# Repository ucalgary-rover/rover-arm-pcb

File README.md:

# rover-arm-pcb

A custom robot arm control PCB for the 2023 SSRT rover.

## Features
* Onboard microcontroller breakout board, like an Arduino Mega or similar
* Controls up to:
    * 7x NEMA23 stepper motors
    * 2x servo motors
    * 7x limit switches
    * A spotlight
    * Other peripherals, like grip strength load cell sensors
* Per-motor current sensing capabilities
* Integrates with off-the-shelf stepper motor drivers (TB6560) and custom circuitry for high reliability and ease of assembly

## Methodology
* PCB is designed in KiCAD v7.0.
* PCB design is used as a teaching tool, so simplicity and likelihood of success was prioritized

## Dependencies
https://github.com/Alarm-Siren/arduino-kicad-library

## Opportunities for Impovement
* Use an encoder/decoder for the EN pins, instead of using so many pins on the microcontroller.

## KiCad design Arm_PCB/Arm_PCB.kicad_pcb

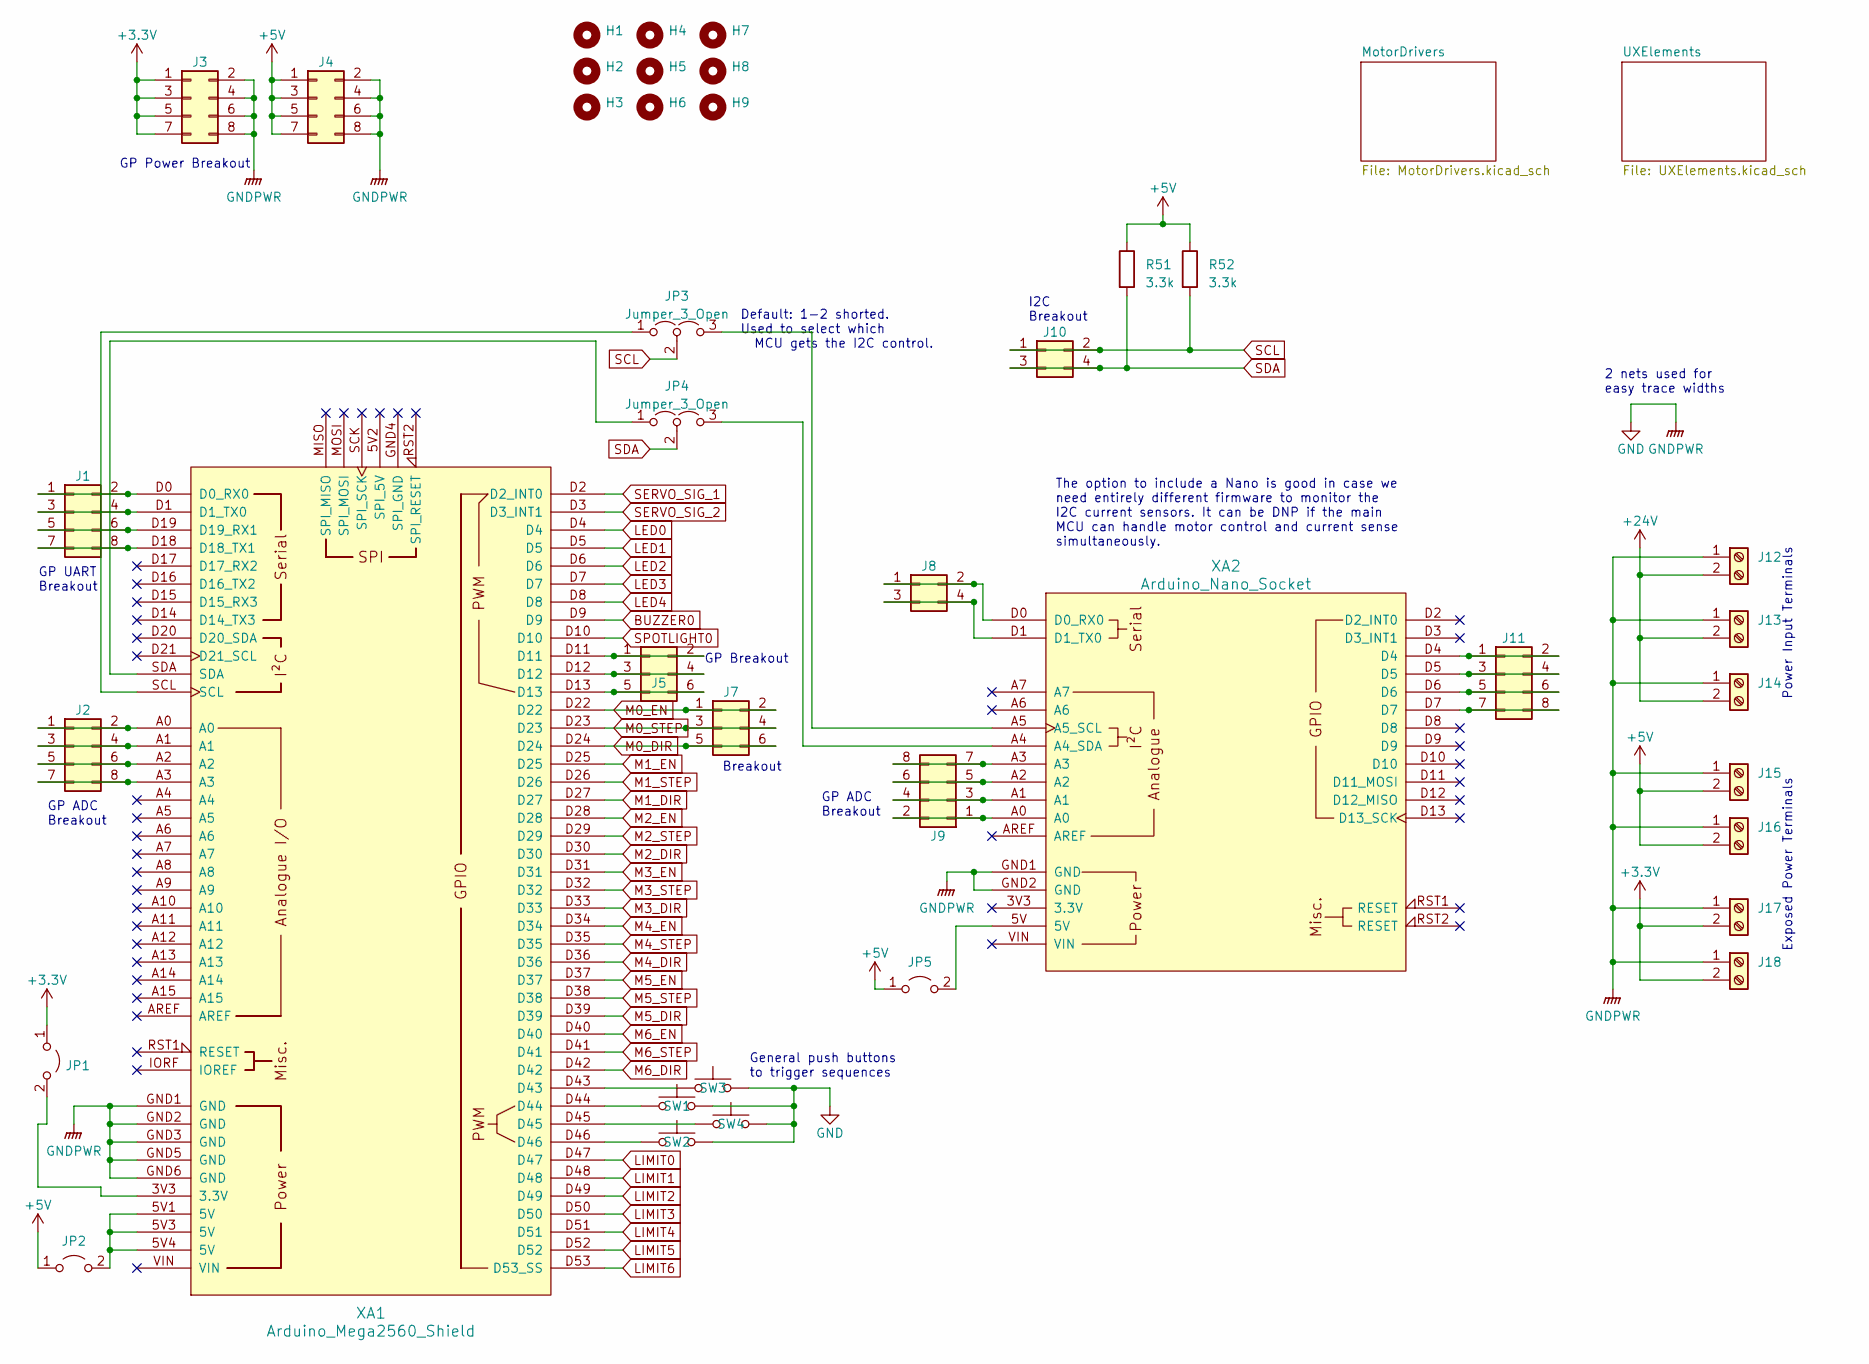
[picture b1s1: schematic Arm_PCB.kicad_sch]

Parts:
H1, H2, H3, H4, H5, H6, H7, H8, H9: MountingHole; MountingHole_4.3mm_M4
J1, J2, J3, J4, J9, J11: Conn_02x04_Counter_Clockwise; PinHeader_2x04_P2.54mm_Vertical
J5, J7: Conn_02x03_Counter_Clockwise; PinHeader_2x03_P2.54mm_Vertical
J8, J10: Conn_02x02_Counter_Clockwise; PinHeader_2x02_P2.54mm_Vertical
J12, J13, J14, J15, J16, J17, J18: Screw_Terminal_01x02; TerminalBlock_bornier-2_P5.08mm
JP1, JP2, JP5: Jumper_2_Open; PinHeader_1x02_P2.54mm_Vertical
JP3, JP4: Jumper_3_Open; PinHeader_1x03_P2.54mm_Vertical
R51, R52: 3.3k; R_1206_3216Metric_Pad1.30x1.75mm_HandSolder
SW1, SW2, SW3, SW4: SW_Push; SW_PUSH_6mm
XA1: Arduino_Mega2560_Shield
XA2: Arduino_Nano_Socket

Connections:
+3.3V: J3.1, J3.3, J3.5, J3.7, J17.2, J18.2, JP1.1 (A); also elsewhere on the board
+5V: J4.1, J4.3, J4.5, J4.7, J15.2, J16.2, JP2.1 (A), JP5.1 (A), R51.1, R52.1; also elsewhere on the board
+24V: J12.2, J13.2, J14.2; also elsewhere on the board
BUZZER0: XA1.D9; also elsewhere on the board
GND: J3.2, J3.4, J3.6, J3.8, J4.2, J4.4, J4.6, J4.8, J12.1, J13.1, J14.1, J15.1, J16.1, J17.1, J18.1, SW1.2, SW2.2, SW3.2, SW4.2, XA1.GND1 (GND), XA1.GND2 (GND), XA1.GND3 (GND), XA1.GND5 (GND), XA1.GND6 (GND), XA2.GND1 (GND), XA2.GND2 (GND); also elsewhere on the board
LED0: XA1.D4; also elsewhere on the board
LED1: XA1.D5; also elsewhere on the board
LED2: XA1.D6; also elsewhere on the board
LED3: XA1.D7; also elsewhere on the board
LED4: XA1.D8; also elsewhere on the board
LIMIT0: XA1.D47; also elsewhere on the board
LIMIT1: XA1.D48; also elsewhere on the board
LIMIT2: XA1.D49; also elsewhere on the board
LIMIT3: XA1.D50; also elsewhere on the board
LIMIT4: XA1.D51; also elsewhere on the board
LIMIT5: XA1.D52; also elsewhere on the board
LIMIT6: XA1.D53 (D53_SS); also elsewhere on the board
M0_DIR: J7.5, J7.6, XA1.D24; also elsewhere on the board
M0_EN: J7.1, J7.2, XA1.D22; also elsewhere on the board
M0_STEP: J7.3, J7.4, XA1.D23; also elsewhere on the board
M1_DIR: XA1.D27; also elsewhere on the board
M1_EN: XA1.D25; also elsewhere on the board
M1_STEP: XA1.D26; also elsewhere on the board
M2_DIR: XA1.D30; also elsewhere on the board
M2_EN: XA1.D28; also elsewhere on the board
M2_STEP: XA1.D29; also elsewhere on the board
M3_DIR: XA1.D33; also elsewhere on the board
M3_EN: XA1.D31; also elsewhere on the board
M3_STEP: XA1.D32; also elsewhere on the board
M4_DIR: XA1.D36; also elsewhere on the board
M4_EN: XA1.D34; also elsewhere on the board
M4_STEP: XA1.D35; also elsewhere on the board
M5_DIR: XA1.D39; also elsewhere on the board
M5_EN: XA1.D37; also elsewhere on the board
M5_STEP: XA1.D38; also elsewhere on the board
M6_DIR: XA1.D42; also elsewhere on the board
M6_EN: XA1.D40; also elsewhere on the board
M6_STEP: XA1.D41; also elsewhere on the board
unnamed: J1.1, J1.2, XA1.D0 (D0_RX0)
unnamed: J1.3, J1.4, XA1.D1 (D1_TX0)
unnamed: J1.5, J1.6, XA1.D19 (D19_RX1)
unnamed: J1.7, J1.8, XA1.D18 (D18_TX1)
unnamed: J2.1, J2.2, XA1.A0
unnamed: J2.3, J2.4, XA1.A1
unnamed: J2.5, J2.6, XA1.A2
unnamed: J2.7, J2.8, XA1.A3
unnamed: J5.1, J5.2, XA1.D11
unnamed: J5.3, J5.4, XA1.D12
unnamed: J5.5, J5.6, XA1.D13
unnamed: J8.1, J8.2, XA2.D0 (D0_RX0)
unnamed: J8.3, J8.4, XA2.D1 (D1_TX0)
unnamed: J9.1, J9.2, XA2.A0
unnamed: J9.3, J9.4, XA2.A1
unnamed: J9.5, J9.6, XA2.A2
unnamed: J9.7, J9.8, XA2.A3
unnamed: J11.1, J11.2, XA2.D4
unnamed: J11.3, J11.4, XA2.D5
unnamed: J11.5, J11.6, XA2.D6
unnamed: J11.7, J11.8, XA2.D7
unnamed: JP1.2 (B), XA1.3V3 (3.3V)
unnamed: JP2.2 (B), XA1.5V1 (5V), XA1.5V3 (5V), XA1.5V4 (5V)
unnamed: JP3.1 (A), XA1.SCL
unnamed: JP3.3 (B), XA2.A5 (A5_SCL)
unnamed: JP4.1 (A), XA1.SDA
unnamed: JP4.3 (B), XA2.A4 (A4_SDA)
unnamed: JP5.2 (B), XA2.5V
unnamed: SW1.1, XA1.D44
unnamed: SW2.1, XA1.D46
unnamed: SW3.1, XA1.D43
unnamed: SW4.1, XA1.D45
SCL: J10.1, J10.2, JP3.2 (C), R52.2; also elsewhere on the board
SDA: J10.3, J10.4, JP4.2 (C), R51.2; also elsewhere on the board
SERVO_SIG_1: XA1.D2 (D2_INT0); also elsewhere on the board
SERVO_SIG_2: XA1.D3 (D3_INT1); also elsewhere on the board
SPOTLIGHT0: XA1.D10; also elsewhere on the board

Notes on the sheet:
Exposed Power Terminals
The option to include a Nano is good in case we need entirely different firmware to monitor the I2C current sensors. It can be DNP if the main MCU can handle motor control and current sense simultaneously.
General push buttons to trigger sequences
GP UART Breakout
GP Breakout
Default: 1-2 shorted. Used to select which MCU gets the I2C control.
2 nets used for easy trace widths
GP Power Breakout
GP ADC Breakout
I2C Breakout
Breakout
Power Input Terminals

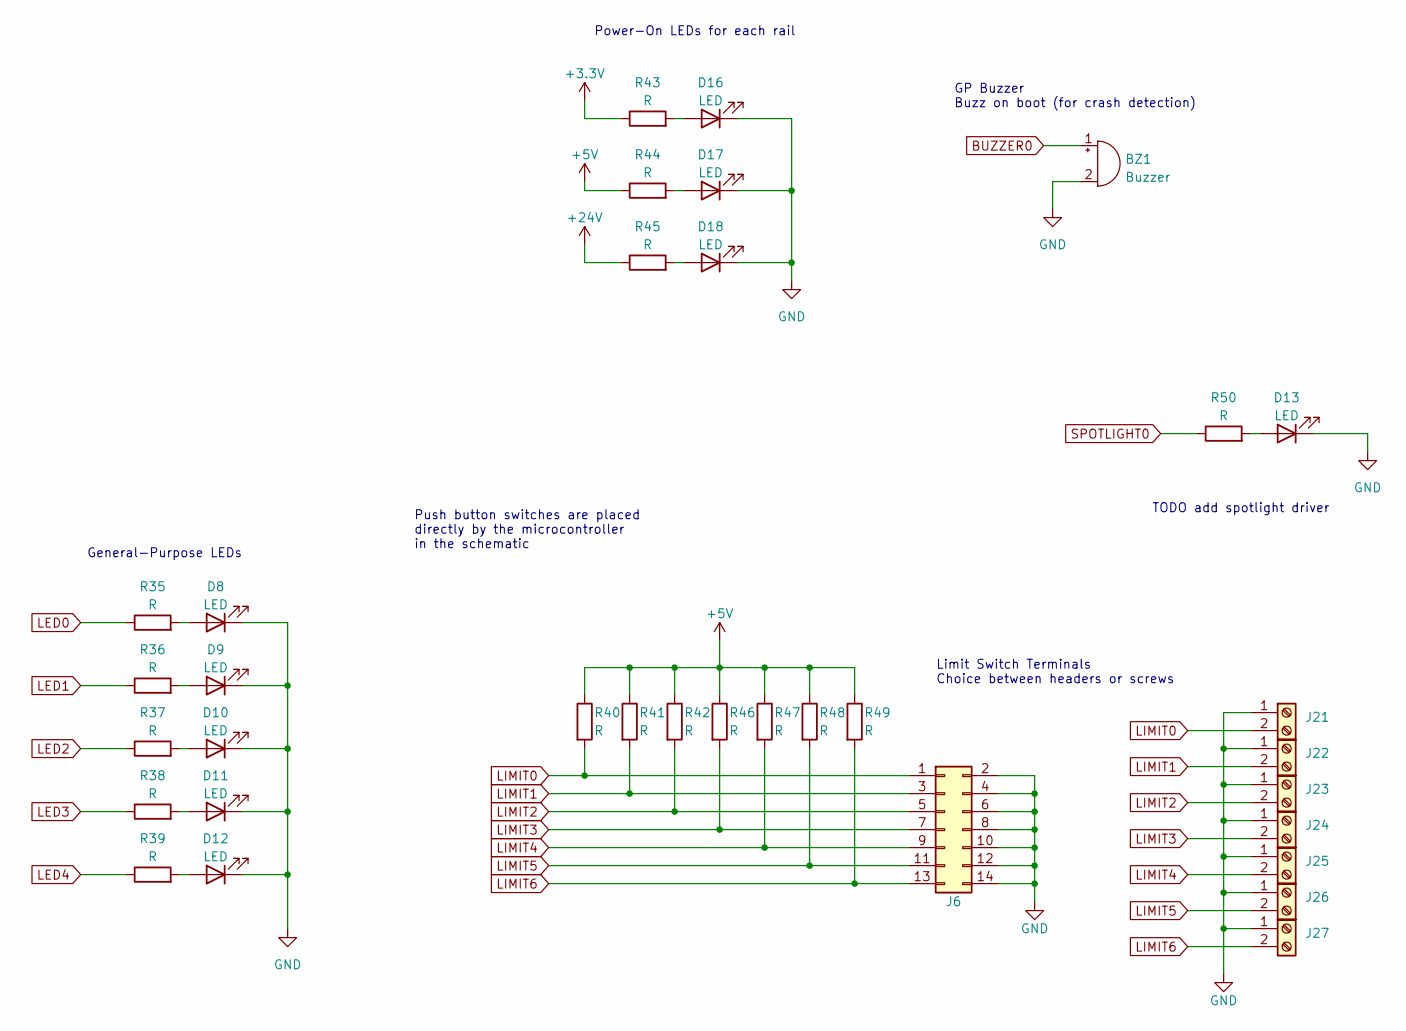
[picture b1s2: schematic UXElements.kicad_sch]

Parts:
BZ1: Buzzer; Buzzer_15x7.5RM7.6
D8, D9, D10, D11, D12, D13, D16, D17, D18: LED; LED_1206_3216Metric_Pad1.42x1.75mm_HandSolder
J6: Conn_02x07_Counter_Clockwise; PinHeader_2x07_P2.54mm_Vertical
J21, J22, J23, J24, J25, J26, J27: Screw_Terminal_01x02; TerminalBlock_bornier-2_P5.08mm
R35, R36, R37, R38, R39, R40, R41, R42, R43, R44, R45, R46, R47, R48, R49, R50: R; R_1206_3216Metric_Pad1.30x1.75mm_HandSolder

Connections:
+3.3V: R43.1; also elsewhere on the board
+5V: R40.1, R41.1, R42.1, R44.1, R46.1, R47.1, R48.1, R49.1; also elsewhere on the board
+24V: R45.1; also elsewhere on the board
BUZZER0: BZ1.1 (-); also elsewhere on the board
GND: BZ1.2 (+), D8.1 (K), D9.1 (K), D10.1 (K), D11.1 (K), D12.1 (K), D13.1 (K), D16.1 (K), D17.1 (K), D18.1 (K), J6.2, J6.4, J6.6, J6.8, J6.10, J6.12, J6.14, J21.1, J22.1, J23.1, J24.1, J25.1, J26.1, J27.1; also elsewhere on the board
LED0: R35.1; also elsewhere on the board
LED1: R36.1; also elsewhere on the board
LED2: R37.1; also elsewhere on the board
LED3: R38.1; also elsewhere on the board
LED4: R39.1; also elsewhere on the board
LIMIT0: J6.1, J21.2, R40.2; also elsewhere on the board
LIMIT1: J6.3, J22.2, R41.2; also elsewhere on the board
LIMIT2: J6.5, J23.2, R42.2; also elsewhere on the board
LIMIT3: J6.7, J24.2, R46.2; also elsewhere on the board
LIMIT4: J6.9, J25.2, R47.2; also elsewhere on the board
LIMIT5: J6.11, J26.2, R48.2; also elsewhere on the board
LIMIT6: J6.13, J27.2, R49.2; also elsewhere on the board
unnamed: D8.2 (A), R35.2
unnamed: D9.2 (A), R36.2
unnamed: D10.2 (A), R37.2
unnamed: D11.2 (A), R38.2
unnamed: D12.2 (A), R39.2
unnamed: D13.2 (A), R50.2
unnamed: D16.2 (A), R43.2
unnamed: D17.2 (A), R44.2
unnamed: D18.2 (A), R45.2
SPOTLIGHT0: R50.1; also elsewhere on the board

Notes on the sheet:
Push button switches are placed directly by the microcontroller in the schematic
Power-On LEDs for each rail
TODO add spotlight driver
Limit Switch Terminals Choice between headers or screws
GP Buzzer Buzz on boot (for crash detection)
General-Purpose LEDs

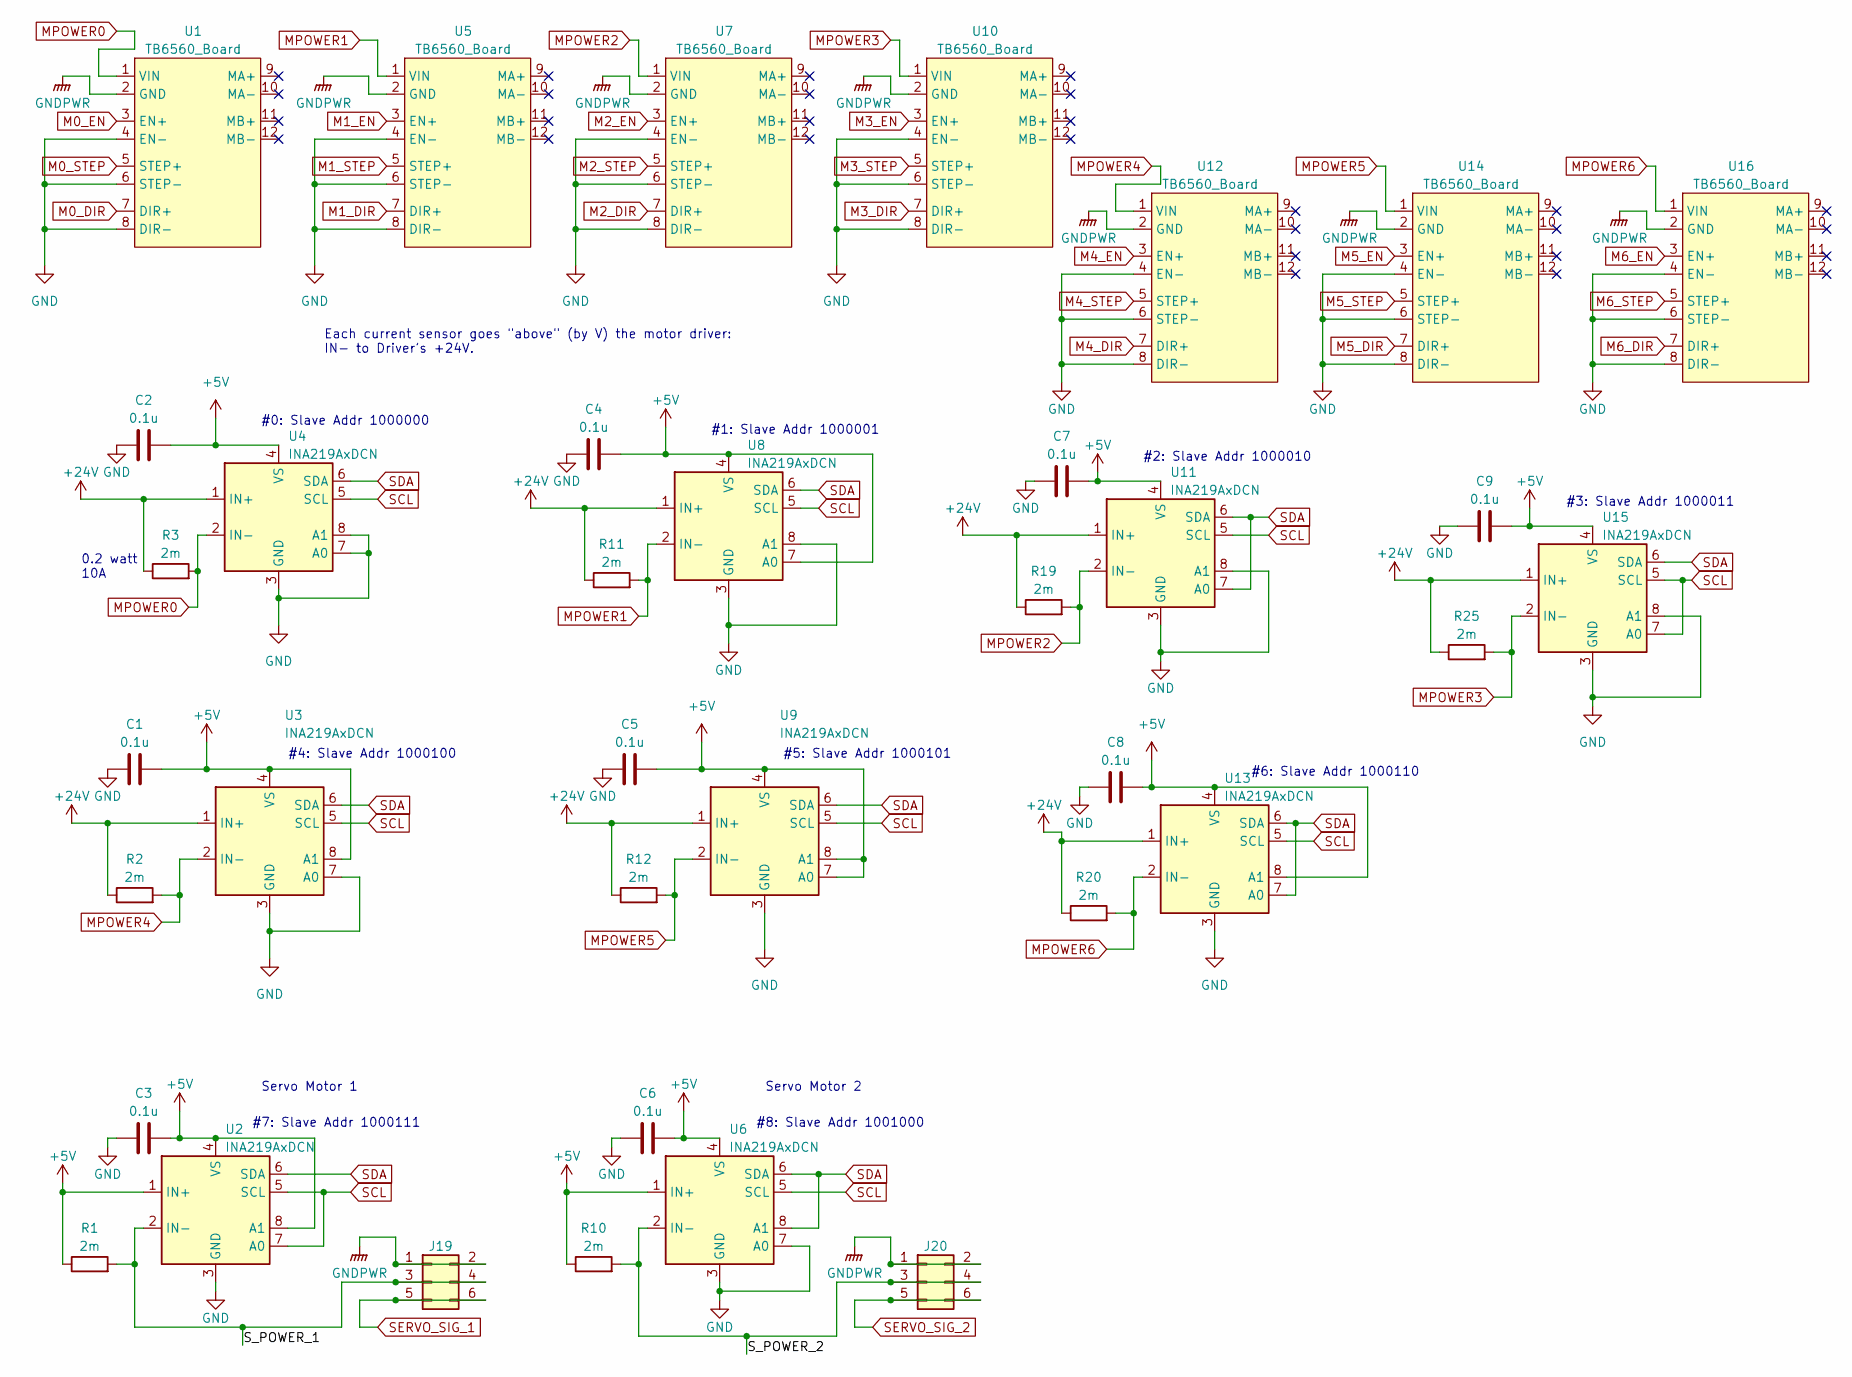
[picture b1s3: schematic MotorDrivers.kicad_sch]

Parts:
C1, C2, C3, C4, C5, C6, C7, C8, C9: 0.1u; C_1206_3216Metric_Pad1.33x1.80mm_HandSolder
J19, J20: Conn_02x03_Counter_Clockwise; PinHeader_2x03_P2.54mm_Vertical
R1, R2, R3, R10, R11, R12, R19, R20, R25: 2m; R_1206_3216Metric_Pad1.30x1.75mm_HandSolder
U1, U16: TB6560_Board; TB6600_Breakout
U2, U3, U4, U6, U8, U9, U11, U13, U15: INA219AxDCN; SOIC-8_3.9x4.9mm_P1.27mm
U5, U7, U10, U12, U14: TB6560_Board; TB6560_Breakout

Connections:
+5V: C1.1, C2.1, C3.1, C4.1, C5.1, C6.1, C7.1, C8.1, C9.1, R1.1, R10.1, U2.1 (IN+), U2.4 (VS), U2.8 (A1), U3.4 (VS), U3.8 (A1), U4.4 (VS), U6.1 (IN+), U6.4 (VS), U8.4 (VS), U8.7 (A0), U9.4 (VS), U9.7 (A0), U9.8 (A1), U11.4 (VS), U13.4 (VS), U13.8 (A1), U15.4 (VS); also elsewhere on the board
+24V: R2.1, R3.1, R11.1, R12.1, R19.1, R20.1, R25.1, U3.1 (IN+), U4.1 (IN+), U8.1 (IN+), U9.1 (IN+), U11.1 (IN+), U13.1 (IN+), U15.1 (IN+); also elsewhere on the board
/MotorDrivers/S_POWER_1: J19.3, J19.4, R1.2, U2.2 (IN-)
/MotorDrivers/S_POWER_2: J20.3, J20.4, R10.2, U6.2 (IN-)
GND: C1.2, C2.2, C3.2, C4.2, C5.2, C6.2, C7.2, C8.2, C9.2, J19.1, J19.2, J20.1, J20.2, U1.2 (GND), U1.4 (EN-), U1.6 (STEP-), U1.8 (DIR-), U2.3 (GND), U3.3 (GND), U3.7 (A0), U4.3 (GND), U4.7 (A0), U4.8 (A1), U5.2 (GND), U5.4 (EN-), U5.6 (STEP-), U5.8 (DIR-), U6.3 (GND), U6.7 (A0), U7.2 (GND), U7.4 (EN-), U7.6 (STEP-), U7.8 (DIR-), U8.3 (GND), U8.8 (A1), U9.3 (GND), U10.2 (GND), U10.4 (EN-), U10.6 (STEP-), U10.8 (DIR-), U11.3 (GND), U11.8 (A1), U12.2 (GND), U12.4 (EN-), U12.6 (STEP-), U12.8 (DIR-), U13.3 (GND), U14.2 (GND), U14.4 (EN-), U14.6 (STEP-), U14.8 (DIR-), U15.3 (GND), U15.8 (A1), U16.2 (GND), U16.4 (EN-), U16.6 (STEP-), U16.8 (DIR-); also elsewhere on the board
M0_DIR: U1.7 (DIR+); also elsewhere on the board
M0_EN: U1.3 (EN+); also elsewhere on the board
M0_STEP: U1.5 (STEP+); also elsewhere on the board
M1_DIR: U5.7 (DIR+); also elsewhere on the board
M1_EN: U5.3 (EN+); also elsewhere on the board
M1_STEP: U5.5 (STEP+); also elsewhere on the board
M2_DIR: U7.7 (DIR+); also elsewhere on the board
M2_EN: U7.3 (EN+); also elsewhere on the board
M2_STEP: U7.5 (STEP+); also elsewhere on the board
M3_DIR: U10.7 (DIR+); also elsewhere on the board
M3_EN: U10.3 (EN+); also elsewhere on the board
M3_STEP: U10.5 (STEP+); also elsewhere on the board
M4_DIR: U12.7 (DIR+); also elsewhere on the board
M4_EN: U12.3 (EN+); also elsewhere on the board
M4_STEP: U12.5 (STEP+); also elsewhere on the board
M5_DIR: U14.7 (DIR+); also elsewhere on the board
M5_EN: U14.3 (EN+); also elsewhere on the board
M5_STEP: U14.5 (STEP+); also elsewhere on the board
M6_DIR: U16.7 (DIR+); also elsewhere on the board
M6_EN: U16.3 (EN+); also elsewhere on the board
M6_STEP: U16.5 (STEP+); also elsewhere on the board
MPOWER0: R3.2, U1.1 (VIN), U4.2 (IN-)
MPOWER1: R11.2, U5.1 (VIN), U8.2 (IN-)
MPOWER2: R19.2, U7.1 (VIN), U11.2 (IN-)
MPOWER3: R25.2, U10.1 (VIN), U15.2 (IN-)
MPOWER4: R2.2, U3.2 (IN-), U12.1 (VIN)
MPOWER5: R12.2, U9.2 (IN-), U14.1 (VIN)
MPOWER6: R20.2, U13.2 (IN-), U16.1 (VIN)
SCL: U2.5 (SCL), U2.7 (A0), U3.5 (SCL), U4.5 (SCL), U6.5 (SCL), U8.5 (SCL), U9.5 (SCL), U11.5 (SCL), U13.5 (SCL), U15.5 (SCL), U15.7 (A0); also elsewhere on the board
SDA: U2.6 (SDA), U3.6 (SDA), U4.6 (SDA), U6.6 (SDA), U6.8 (A1), U8.6 (SDA), U9.6 (SDA), U11.6 (SDA), U11.7 (A0), U13.6 (SDA), U13.7 (A0), U15.6 (SDA); also elsewhere on the board
SERVO_SIG_1: J19.5, J19.6; also elsewhere on the board
SERVO_SIG_2: J20.5, J20.6; also elsewhere on the board

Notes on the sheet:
#1: Slave Addr 1000001
Servo Motor 2
Each current sensor goes "above" (by V) the motor driver: IN- to Driver's +24V.
Servo Motor 1
#8: Slave Addr 1001000
#0: Slave Addr 1000000
0.2 watt 10A
#7: Slave Addr 1000111
#6: Slave Addr 1000110
#2: Slave Addr 1000010
#3: Slave Addr 1000011
#5: Slave Addr 1000101
#4: Slave Addr 1000100

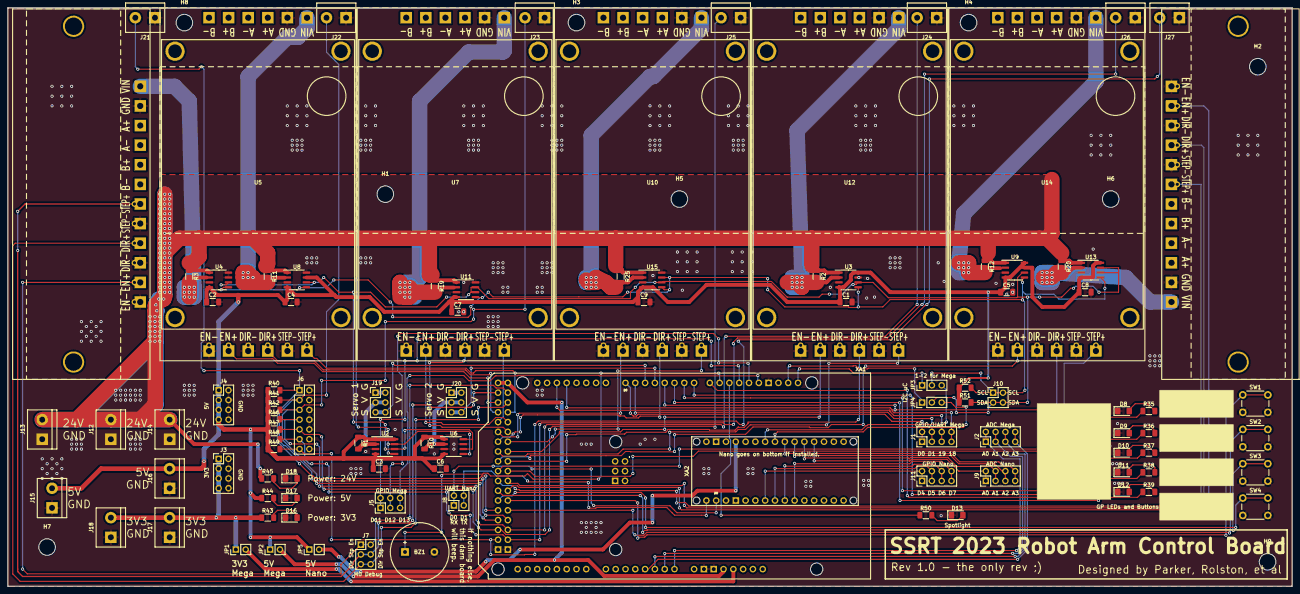
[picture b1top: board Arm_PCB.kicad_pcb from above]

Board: 2 copper layers, 332.7 x 149.9 mm, 109 parts (1 on the bottom side), 93 nets.

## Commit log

2023-02-25 Add initial files
2023-02-25 Added motor controllers and the micro-controllers"
2023-02-27 Added the INA219 schematics,fixed the TB6560 board, added LED for the EN pin on the microcontroller
2023-03-03 Changes, migrate to KiCad v7
2023-03-03 Changes, including UX and breakout pins
2023-03-03 Add PDF plot
2023-03-03 Add servo current sensors, etc.
2023-03-04 Create README.md
    Add readme
2023-03-04 Update footprint library
2023-03-04 Annotate all pages
2023-03-04 Add annotations
2023-03-04 Add spotlight and resistors on limit switches
2023-03-04 Added a basic footprint for the PCB
2023-03-05 Create good footprint for TB6560 driver
2023-03-11 Grouped parts in the PCB sketch to begin routing
2023-03-12 Continue layout, pick some components
2023-03-16 Add TB6600 footprint from online refs
2023-03-16 Footprint updates with new TB6600
2023-03-16 Remove resistors for setting I2C addrs
2023-03-16 Update layout
2023-03-16 Start routing
2023-03-16 Route more
2023-03-16 Render PDFs
2023-03-17 Route more, move uC to middle
2023-03-17 Route nearly whole thing
2023-03-17 Continue routing and cleanup
2023-03-17 Work
2023-03-17 Finish PCB haha
2023-03-18 Add mounting holes, other minor changes
2023-03-18 minor trace width and thermal relief changes
2023-03-22 Add gerber
